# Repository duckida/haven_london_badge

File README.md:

# haven london PCB badge
This is a PCB attendee badge for [Hack Club Haven London](haven.london)!

I spent 2.5hrs designing this in Excalidraw and KiCAD!

It has silkscreen designs, a space to write your name, bare copper Daven (ooh shiny), and optional places to add electronics:
- CR2032 battery holder
- 2x 5mm LEDs
- 47Ω resistor
- Push button to turn them on

The PCB production was sponsored by PCBWay, thank you sm!

AI disclosure: no art or PCB design was done by AI, only the resistor calculation was

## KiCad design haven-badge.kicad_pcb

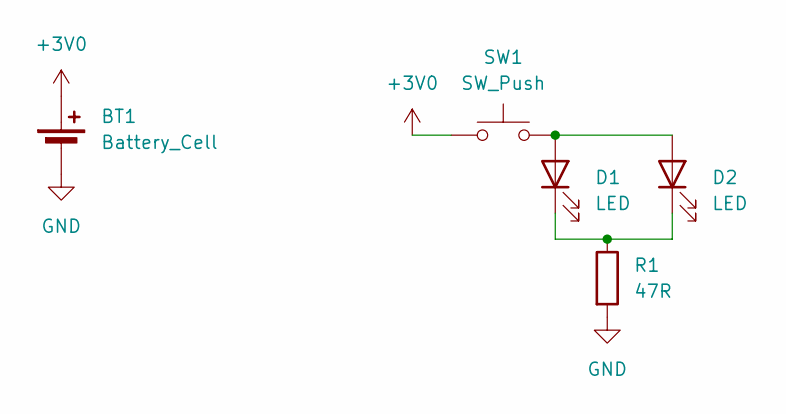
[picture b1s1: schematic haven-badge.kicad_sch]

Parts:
BT1: Battery_Cell; BatteryHolder_Multicomp_BC-2001_1x2032
D1, D2: LED; LED_D5.0mm
R1: 47R; R_Axial_DIN0207_L6.3mm_D2.5mm_P10.16mm_Horizontal
SW1: SW_Push; SW_SPST_PTS645Sx43SMTR92

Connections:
+3V0: BT1.1 (+), SW1.1
GND: BT1.2 (-), R1.2
unnamed: D1.2 (A), D2.2 (A), SW1.2
unnamed: D1.1 (K), D2.1 (K), R1.1

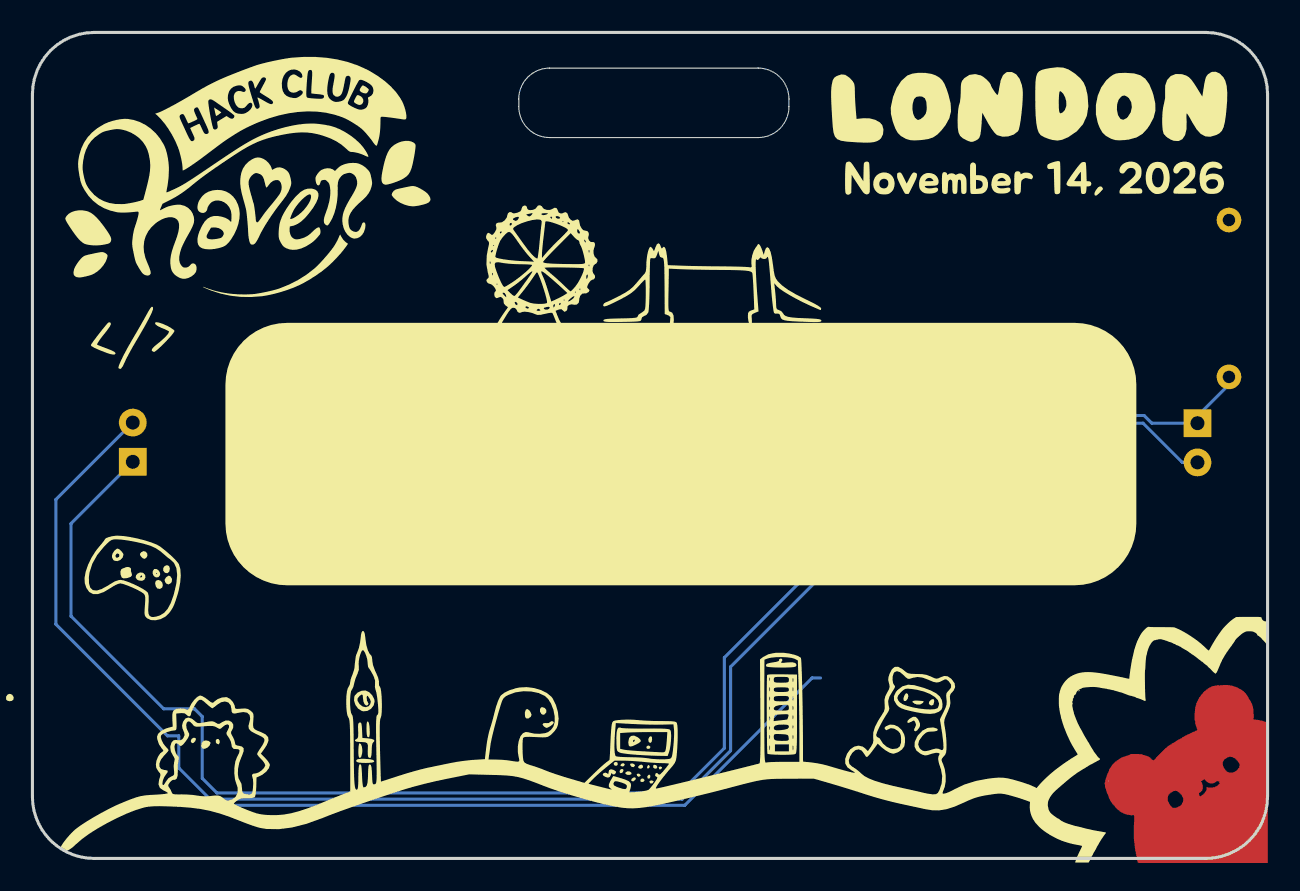
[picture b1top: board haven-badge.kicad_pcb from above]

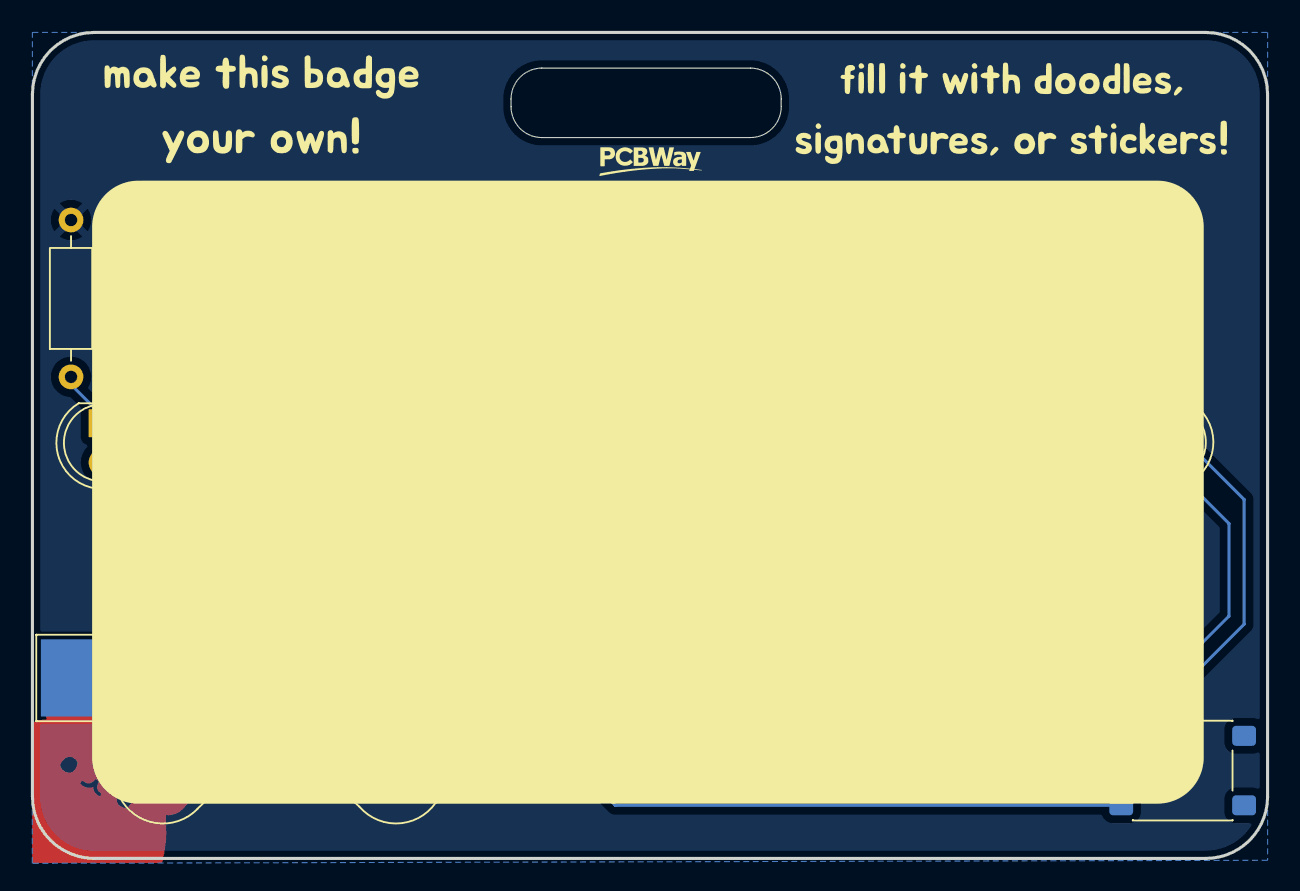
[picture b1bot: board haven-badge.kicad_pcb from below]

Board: 2 copper layers, 80.0 x 53.5 mm, 5 parts (5 on the bottom side), 4 nets.
